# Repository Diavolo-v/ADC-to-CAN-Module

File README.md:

# ADC-to-CAN-Module
Design of a compact ADC-toCAN measurement module for Formula Student

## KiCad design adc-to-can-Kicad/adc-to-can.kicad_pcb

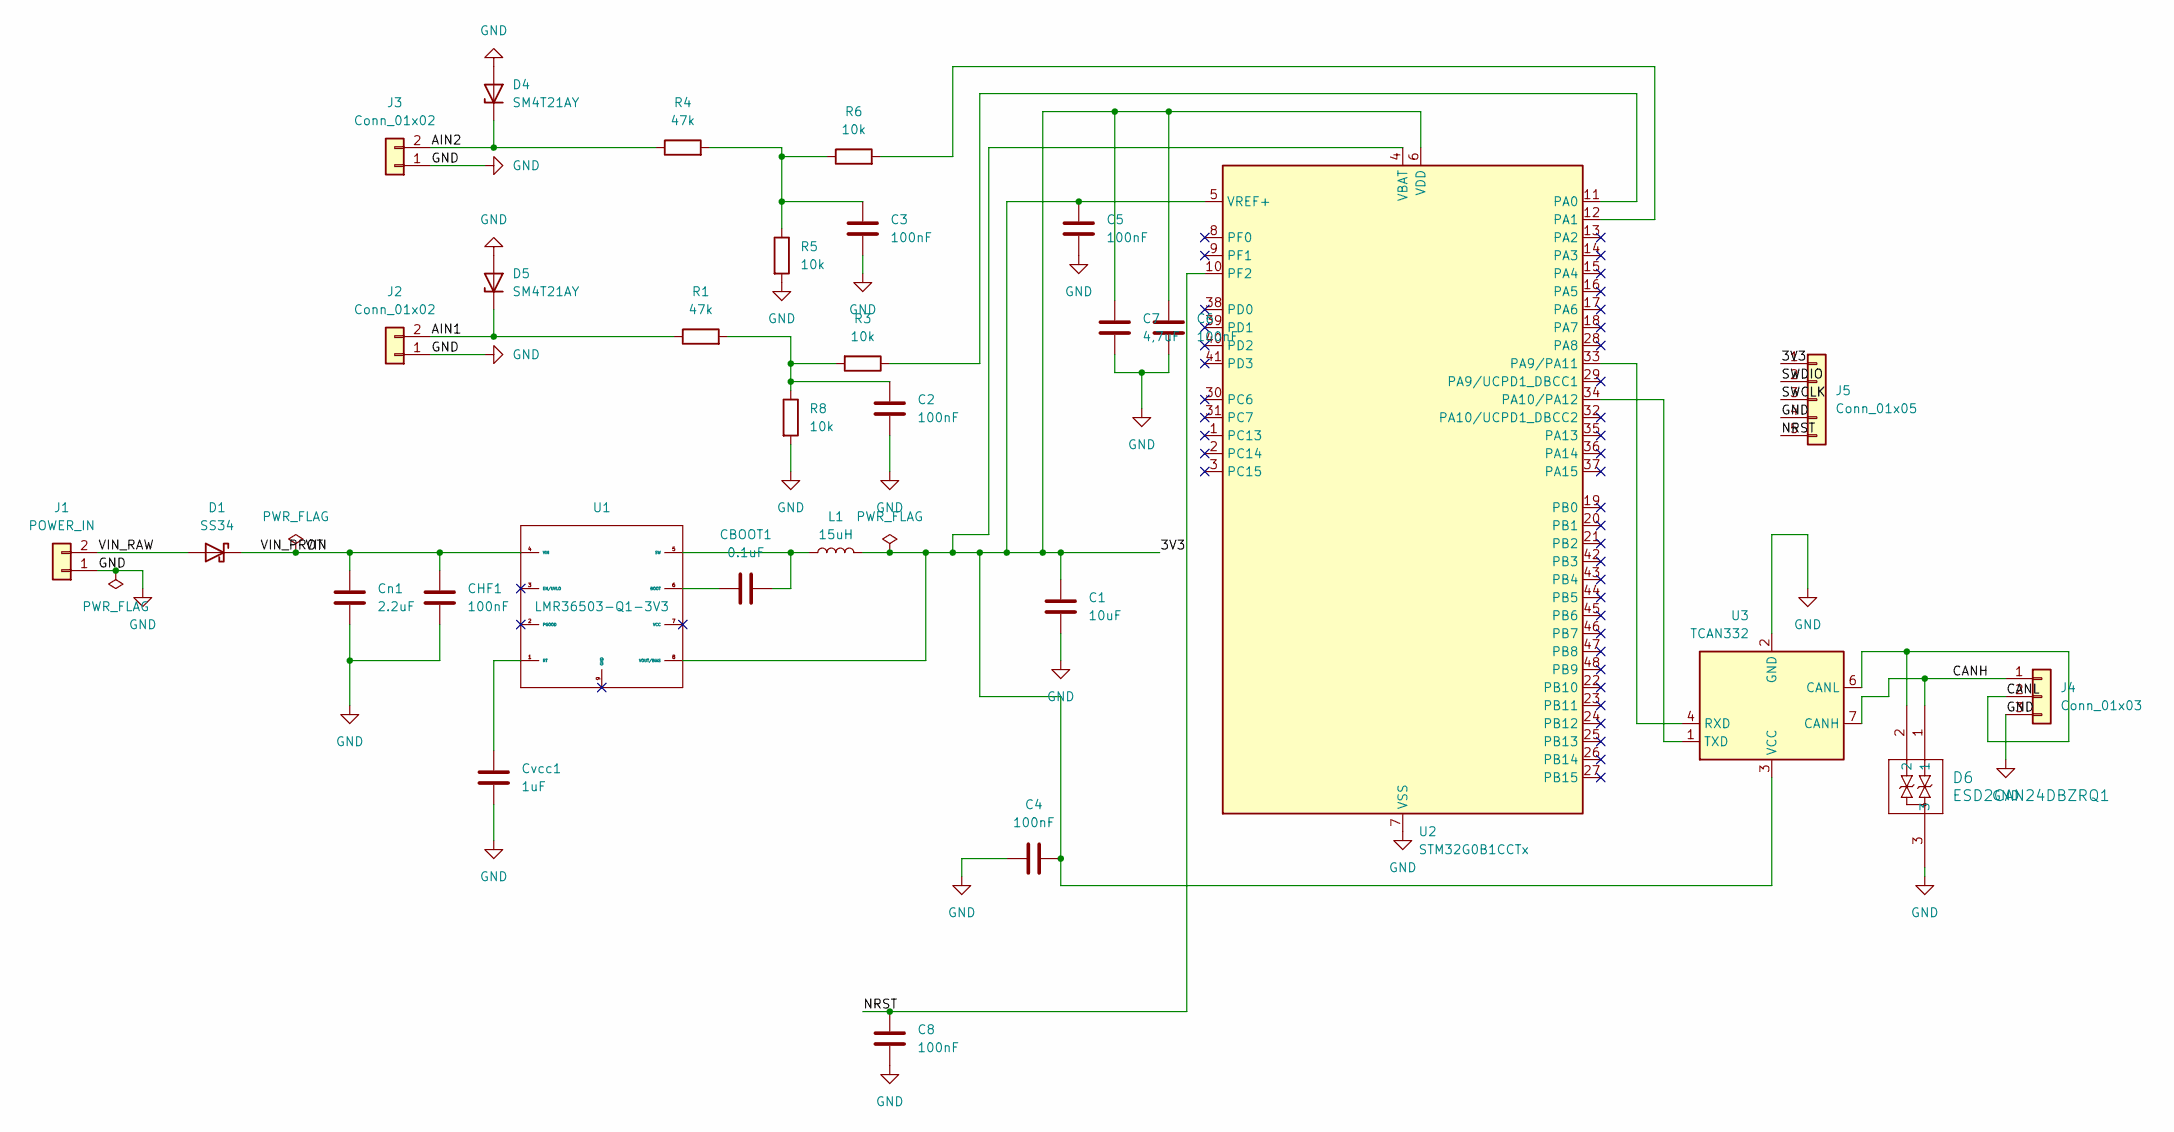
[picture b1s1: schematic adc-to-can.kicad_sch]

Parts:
C1: 10uF; C_0805_2012Metric
C2, C3, C4, C5, C6, C8: 100nF; C_0603_1608Metric
C7: 4,7uF; C_0805_2012Metric
CBOOT1: 0.1uF; C_0603_1608Metric
CHF1: 100nF; C_0603_1608Metric
Cn1: 2.2uF; C_0805_2012Metric
Cvcc1: 1uF; C_0603_1608Metric
D1: SS34; D_SMA
D4, D5: SM4T21AY; D_SMA
D6: ESD2CAN24DBZRQ1; SOT-23_DBZ_TEX
J1: POWER_IN; CONN2_WR-TBL-SERIES101_691101710002_WRE
J2, J3: Conn_01x02; JST_XH_B2B-XH-A_1x02_P2.50mm_Vertical
J4: Conn_01x03; CONN3x1_691101710003_WRE
J5: Conn_01x05; JST_XH_B5B-XH-A_1x05_P2.50mm_Vertical
L1: 15uH; L_Wurth_WE-LQSH-3012
R1, R4: 47k; R_0603_1608Metric
R3, R5, R6, R8: 10k; R_0603_1608Metric
U1: LMR36503-Q1-3V3; RPE0009A
U2: STM32G0B1CCTx; LQFP-48_7x7mm_P0.5mm
U3: TCAN332; SOIC-8_3.9x4.9mm_P1.27mm

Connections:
/3V3: C1.1, C4.2, C5.1, C6.1, C7.1, J5.1, L1.2, U1.8 (VOUT/BIAS), U2.4 (VBAT), U2.5 (VREF+), U2.6 (VDD), U3.3 (VCC)
/AIN1: D5.1 (K), J2.2, R1.1
/AIN2: D4.1 (K), J3.2, R4.1
/CANH: D6.1, J4.1, U3.7 (CANH)
/NRST: C8.1, J5.5, U2.10 (PF2)
/SWCLK: J5.3
/SWDIO: J5.2
/VIN: CHF1.1, Cn1.1, D1.1 (K), U1.4 (VIN)
/VIN_RAW: D1.2 (A), J1.2
GND: C1.2, C2.2, C3.2, C4.1, C5.2, C6.2, C7.2, C8.2, CHF1.2, Cn1.2, Cvcc1.2, D4.2 (A), D5.2 (A), D6.3, J1.1, J2.1, J3.1, J4.3, J5.4, R5.2, R8.2, U2.7 (VSS), U3.2 (GND)
unnamed: C2.1, R1.2, R3.2, R8.1
unnamed: C3.1, R4.2, R5.1, R6.1
unnamed: D6.2, J4.2, U3.6 (CANL)
unnamed: CBOOT1.1, U1.6 (BOOT)
unnamed: Cvcc1.1, U1.1 (RT)
unnamed: CBOOT1.2, L1.1, U1.5 (SW)
unnamed: R3.1, U2.11 (PA0)
unnamed: R6.2, U2.12 (PA1)
unnamed: U2.33 (PA9/PA11), U3.4 (RXD)
unnamed: U2.34 (PA10/PA12), U3.1 (TXD)

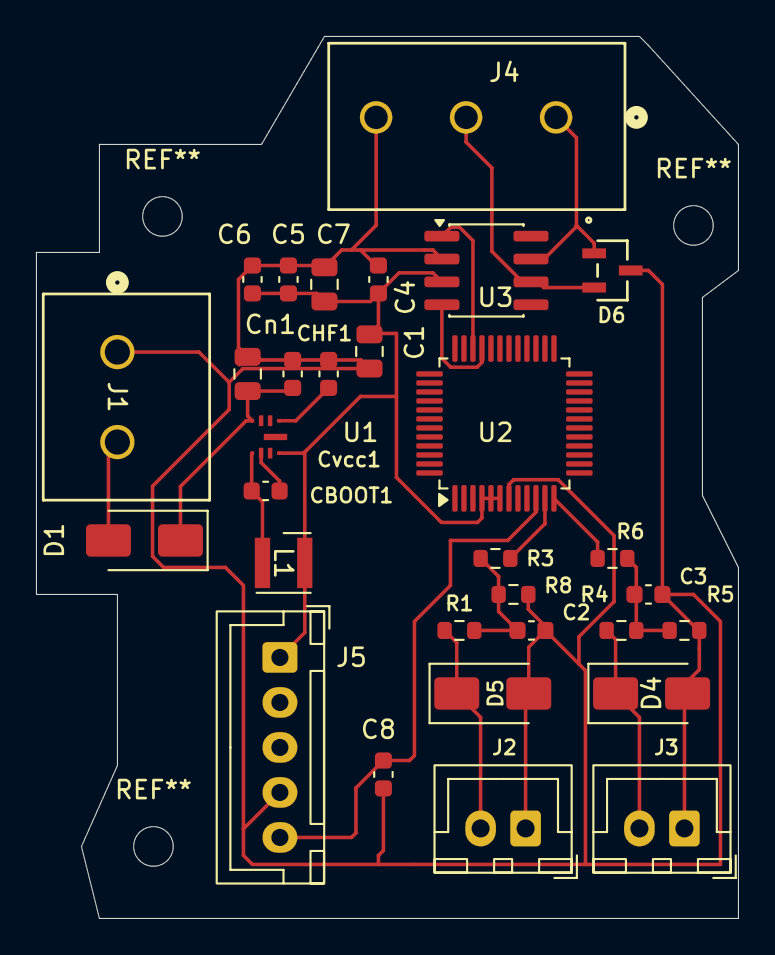
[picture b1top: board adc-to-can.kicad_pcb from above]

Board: 2 copper layers, 39.0 x 49.0 mm, 31 parts (0 on the bottom side), 18 nets.

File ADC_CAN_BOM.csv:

Reference;Qty;Value;DNP;Exclude from BOM;Exclude from Board;Exclude from Simulation;Exclude from Position Files;Footprint;Datasheet
C1;1;10uF;;;;;${EXCLUDE_FROM_POS_FILES};Capacitor_SMD:C_0805_2012Metric;https://product.samsungsem.com/resources/file/product-catalo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
C2,C3,C4,C5,C6,C8,CHF1;7;100nF;;;;;${EXCLUDE_FROM_POS_FILES};Capacitor_SMD:C_0603_1608Metric;https://product.samsungsem.com/resources/file/product-catalo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
C7;1;4,7uF;;;;;${EXCLUDE_FROM_POS_FILES};Capacitor_SMD:C_0805_2012Metric;https://product.samsungsem.com/resources/file/product-catalo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
CBOOT1;1;0.1uF;;;;;${EXCLUDE_FROM_POS_FILES};Capacitor_SMD:C_0603_1608Metric;https://product.samsungsem.com/resources/file/product-catalo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
Cn1;1;2.2uF;;;;;${EXCLUDE_FROM_POS_FILES};Capacitor_SMD:C_0805_2012Metric;https://product.samsungsem.com/resources/file/product-catalo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
Cvcc1;1;1uF;;;;;${EXCLUDE_FROM_POS_FILES};Capacitor_SMD:C_0603_1608Metric;https://product.samsungsem.com/resources/file/product-catalo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
D1;1;SS34;;;;;${EXCLUDE_FROM_POS_FILES};Diode_SMD:D_SMA;https://www.onsemi.com/pdf/datasheet/ss39-d.pdf
D4,D5;2;SM4T21AY;;;;;${EXCLUDE_FROM_POS_FILES};Diode_SMD:D_SMA;https://www.st.com/resource/en/datasheet/cd00283395.pdf
D6;1;ESD2CAN24DBZRQ1;;;;;${EXCLUDE_FROM_POS_FILES};ESD2CAN24DBZRQ1:SOT-23_DBZ_TEX;https://www.ti.com/lit/ds/symlink/esd2can24-q1.pdf?ts=1793166872850
J1;1;POWER_IN;;;;;${EXCLUDE_FROM_POS_FILES};691101710002:CONN2_WR-TBL-SERIES101_691101710002_WRE;https://www.we-online.com/catalog/datasheet/691137710002.pdf
J2,J3;2;Conn_01x02;;;;;${EXCLUDE_FROM_POS_FILES};Connector_JST:JST_XH_B2B-XH-A_1x02_P2.50mm_Vertical;https://www.lcsc.com/datasheet/C158012.pdf
J4;1;Conn_01x03;;;;;${EXCLUDE_FROM_POS_FILES};691101710003:CONN3x1_691101710003_WRE;https://www.we-online.com/components/products/datasheet/6911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
J5;1;Conn_01x05;;;;;${EXCLUDE_FROM_POS_FILES};Connector_JST:JST_XH_B5B-XH-A_1x05_P2.50mm_Vertical;https://www.mouser.pl/datasheet/3/1070/1/eXH.pdf
L1;1;15uH;;;;;${EXCLUDE_FROM_POS_FILES};Inductor_SMD_Wurth:L_Wurth_WE-LQSH-3012;https://www.mouser.pl/datasheet/3/995/1/lps5030.pdf
R1,R4;2;47k;;;;;${EXCLUDE_FROM_POS_FILES};Resistor_SMD:R_0603_1608Metric;https://industrial.panasonic.com/ww/products/pt/anti-sulfura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
R3,R5,R6,R8;4;10k;;;;;${EXCLUDE_FROM_POS_FILES};Resistor_SMD:R_0603_1608Metric;https://industrial.panasonic.com/cdbs/www-data/pdf/RDA0000/A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
U1;1;LMR36503-Q1-3V3;;;;;${EXCLUDE_FROM_POS_FILES};LMR36503MSC3RPERQ1:RPE0009A;https://www.ti.com/lit/ds/symlink/lmr36503e-q1.pdf?ts=179317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
U2;1;STM32G0B1CCTx;;;;;${EXCLUDE_FROM_POS_FILES};Package_QFP:LQFP-48_7x7mm_P0.5mm;https://www.st.com/resource/en/datasheet/stm32g0b1cc.pdf
U3;1;TCAN332;;;;;${EXCLUDE_FROM_POS_FILES};Package_SO:SOIC-8_3.9x4.9mm_P1.27mm;http://www.ti.com/lit/ds/symlink/tcan337.pdf

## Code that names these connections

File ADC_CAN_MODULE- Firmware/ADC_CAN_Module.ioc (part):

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Mcu.Name=STM32G0B1C(B-C-E)Tx
Mcu.Package=LQFP48
Mcu.UserName=STM32G0B1CCTx
PA0.Mode=IN0
PA0.Signal=ADC1_IN0
PA1.Mode=IN1
PA1.Signal=ADC1_IN1
PA11\ [PA9].Mode=FDCAN_Activate
PA11\ [PA9].Signal=FDCAN1_RX
PA12\ [PA10].Mode=FDCAN_Activate
PA12\ [PA10].Signal=FDCAN1_TX
RCC.HSE_VALUE=8000000
RCC.SYSCLKFreq_VALUE=16000000
board=custom
